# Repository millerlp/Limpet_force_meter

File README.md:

Design files, data, and analysis files from the manuscript "Temperature affects susceptibility of intertidal limpets to bird predation"
Rachel J. Pound, Luke P. Miller, Felicia A. King, Jennifer L. Burnaford
Journal of Experimental Biology 2020 : jeb.213595 doi: 10.1242/jeb.213595

R analysis code and data used in the production of the paper are in the 'R_analysis_files_data/' directory. 

Circuit board designs for the three-dimensional force transducer are in the 'Eagle_files/' directory. These files were
produced with the software Eagle, https://www.autodesk.com/products/eagle/overview. This circuit board is designed to 
attach to an Arduino Due in order to operate. 

Software used to run the 3-dimensional force transducer datalogger are in the 'Arduino_files/' directory. These can
be used with the Arduino software available at https://arduino.cc. The subdirectories in the Arduino_files/ directory should be
installed in the user's "Arduino" directory. 

The Arduino programs here require the following libraries to be installed:
https://github.com/millerlp/RTClib
https://github.com/greiman/SdFat

Limpet_force_meter.ino can be loaded onto the Arduino Due to log data from the force transducer.
Limpet_force_calibration.ino can be loaded to both log data and also to provide a calibration routine that will write data to the SD card as the user hangs weights of various masses off of the 3 axes of the transducer. 

Hardware and software authored by Felicia King and Luke Miller, 2015

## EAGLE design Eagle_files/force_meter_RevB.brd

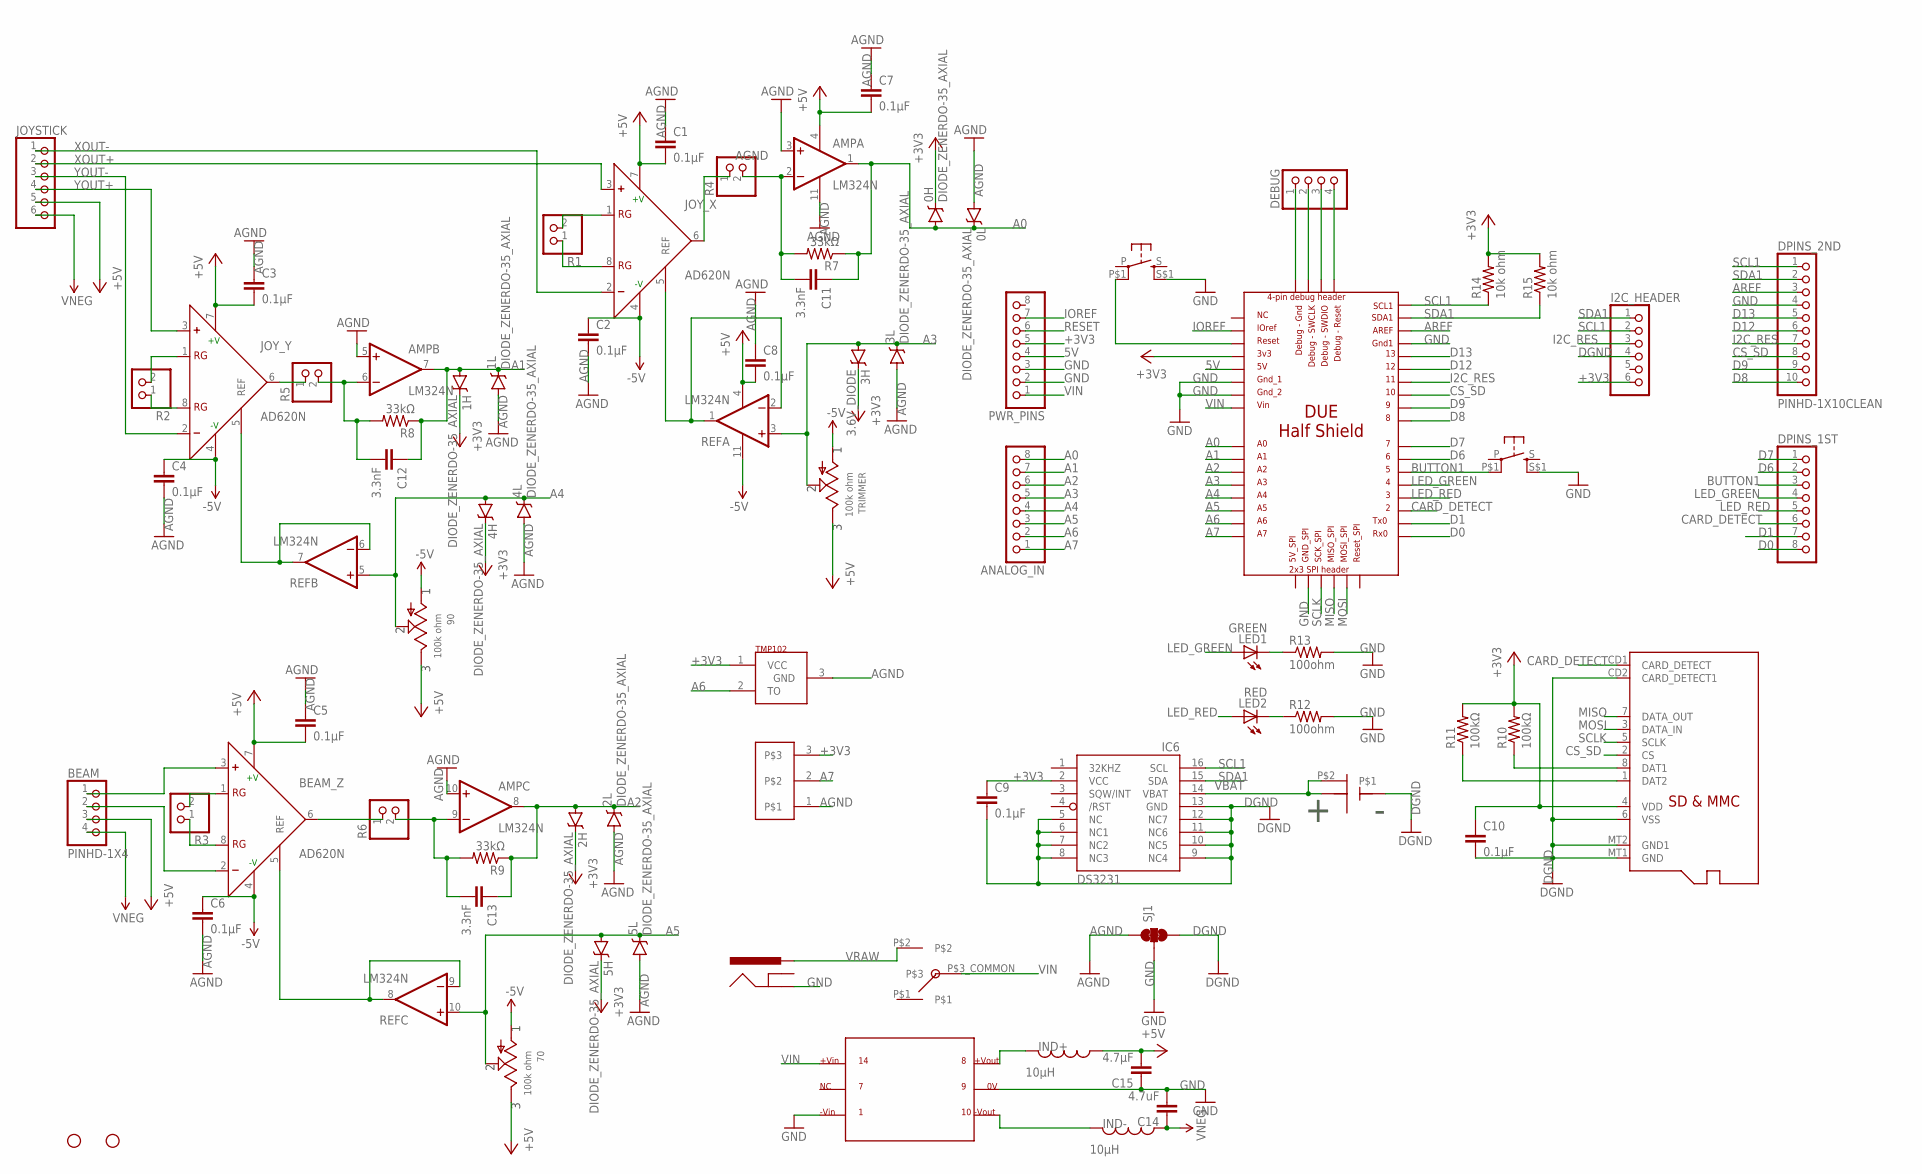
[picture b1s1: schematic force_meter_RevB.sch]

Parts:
0H, 0L, 1H, 1L, 2H, 2L, 3L, 4H, 4L, 5H, 5L: DIODE_ZENERDO-35_AXIAL; DO35-7
3H: 3.6V_DIODE; DO35-7
70, 90: 100k ohm; R-TRIMMER_67W_TT_ELEC
AMP: LM324N; DIL14
ANALOG7_HEADER: PINHD-1X3; 1X03
ANALOG_IN: PINHD-1X8CLEANBIG; 1X08-CLEANBIG
BEAM: PINHD-1X4; 1X04_LOCK
BEAM_Z: AD620N; DIL08
C1, C2, C3, C4, C5, C6, C7, C8, C9, C10: 0.1µF; 0805
C11, C12, C13: 3.3nF; 0805
C14: 4.7uF; 0805
C15: 4.7µF; 0805
DEBUG: PINHD-1X4LOCK; 1X04_LOCK
DPINS_1ST: PINHD-1X8CLEANBIG; 1X08-CLEANBIG
DPINS_2ND: PINHD-1X10CLEAN; 1X10-CLEANBIG
I2C_HEADER: PINHD-1X6LOCK; 1X06-LOCK
IC6: DS3231/SO; SO16W
IND+: 10µH; I_0805
IND-: 10µH; I_0805
INPUT: PUSHBUTTON_DPST_SMD
JOYSTICK: PINHD-1X6LOCK; 1X06-LOCK
JOY_X: AD620N; DIL08
JOY_Y: AD620N; DIL08
LED1: GREEN; CHIPLED_0805
LED2: RED; CHIPLED_0805
PWR_PINS: PINHD-1X8CLEANBIG; 1X08-CLEANBIG
R1, R2, R3, R4, R5, R6: PINHD-1X2; 1X02
R7, R8, R9: 33kΩ; R0805
R10, R11: 100kΩ; R0805
R12, R13: 100ohm; R0805
R14, R15: 10k ohm; R0805
REF: LM324N; DIL14
RESET: PUSHBUTTON; PUSHBUTTON_DPST_SMD
SJ1: JUMPER-PAD-3-NC_BY_TRACE; PAD-JUMPER-3-3OF3_NC_BY_TRACE_YES_SILK_FULL_BOX
STANDOFF1, STANDOFF2: STAND-OFF
TMP102: LM62; SOT23
TRIMMER: 100k ohm; R-TRIMMER_67W_TT_ELEC
U$1: DUE_HALF_SHIELD_A7-ANALOG
U$2: SWITCH_SLIDE_SMD_SPDT; SWITCH_SMD_RA_SPDT
U$3: DC-DC_CONVERTER_DUAL_SUPPLY; DCDC_CONVERTOR-MEV1D
U$11: MICROSD
U$12: CR1220_BATTERY_HOLDERSMD; CR1220_BATTERY_HOLDER_SMD
U$28: POWER_JACK_2,1MM; POWER_JACK_DC_2,1MM

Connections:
5V: PWR_PINS.4, U$1.5V1 (5V)
+3V3: 0H.C, 1H.C, 2H.C, 3H.C, 4H.C, 5H.C, ANALOG7_HEADER.3, C9.1, C10.1, I2C_HEADER.6, IC6.2 (VCC), PWR_PINS.5, R10.2, R11.2, R14.2, R15.2, TMP102.1 (VCC), U$1.3V3, U$11.4 (VDD)
+5V: 70.P$3, 90.P$3, AMP.4 (V+), BEAM.3, BEAM_Z.7 (+V), C1.2, C3.2, C5.2, C7.2, C8.2, C15.2, IND+.P$1 (1), JOYSTICK.5, JOY_X.7 (+V), JOY_Y.7 (+V), REF.4 (V+), TRIMMER.P$3
-5V: 70.P$1, 90.P$1, BEAM.4, BEAM_Z.4 (-V), C6.1, C14.1, IND-.P$1 (1), JOYSTICK.6, TRIMMER.P$1
A0: 0H.A, 0L.C, AMP.1 (OUT), ANALOG_IN.8, C11.1, R7.1, U$1.A0
A1: 1H.A, 1L.C, AMP.7 (OUT), ANALOG_IN.7, C12.1, R8.1, U$1.A1
A2: 2H.A, 2L.C, AMP.8 (OUT), ANALOG_IN.6, C13.1, R9.1, U$1.A2
A3: 3H.A, 3L.C, ANALOG_IN.5, REF.3 (+IN), TRIMMER.P$2, U$1.A3
A4: 4H.A, 4L.C, 90.P$2, ANALOG_IN.4, REF.5 (+IN), U$1.A4
A5: 5H.A, 5L.C, 70.P$2, ANALOG_IN.3, REF.10 (+IN), U$1.A5
A6: ANALOG_IN.2, TMP102.2 (TO), U$1.A6
A7: ANALOG7_HEADER.2, ANALOG_IN.1, U$1.A7
AGND: 0L.A, 1L.A, 2L.A, 3L.A, 4L.A, 5L.A, AMP.3 (+IN), AMP.5 (+IN), AMP.10 (+IN), AMP.11 (V-), ANALOG7_HEADER.1, C1.1, C2.2, C3.1, C4.2, C5.1, C6.2, C7.1, C8.1, SJ1.1, TMP102.3 (GND)
AREF: DPINS_2ND.3, U$1.AREF
BUTTON1: DPINS_1ST.3, INPUT.P$1 (P1), U$1.5
CARD_DETECT: DPINS_1ST.6, U$1.2, U$11.CD1 (CARD_DETECT)
CS_SD: DPINS_2ND.8, U$1.10, U$11.2 (CS)
D0: DPINS_1ST.8, U$1.RX0
D1: DPINS_1ST.7, U$1.TX0
D6: DPINS_1ST.2, U$1.6
D7: DPINS_1ST.1, U$1.7
D8: DPINS_2ND.10, U$1.8
D9: DPINS_2ND.9, U$1.9
D12: DPINS_2ND.6, U$1.12
D13: DPINS_2ND.5, U$1.13
DGND: C9.2, C10.2, I2C_HEADER.4, IC6.5 (NC), IC6.6 (NC1), IC6.7 (NC2), IC6.8 (NC3), IC6.9 (NC4), IC6.10 (NC5), IC6.11 (NC6), IC6.12 (NC7), IC6.13 (GND), SJ1.3, U$11.6 (VSS), U$11.CD2 (CARD_DETECT1), U$11.MT1 (GND), U$11.MT2 (GND1), U$12.GND
GND: C14.2, C15.1, DPINS_2ND.4, INPUT.S$1 (S1), PWR_PINS.2, PWR_PINS.3, R12.2, R13.2, RESET.S$1 (S1), SJ1.2, U$1.GND1, U$1.GND_1, U$1.GND_2, U$1.GND_SPI, U$3.P$1_-VIN, U$3.P$9_0V, U$28.P$2 (GND)
I2C_RES: DPINS_2ND.7, I2C_HEADER.3, U$1.11
IOREF: PWR_PINS.7, U$1.IOREF1 (IOREF)
LED_GREEN: DPINS_1ST.4, LED1.A, U$1.4
LED_RED: DPINS_1ST.5, LED2.A, U$1.3
MISO: U$1.MISO_SPI, U$11.7 (DATA_OUT)
MOSI: U$1.MOSI_SPI, U$11.3 (DATA_IN)
unnamed: JOY_Y.1 (RG), R2.2
unnamed: JOY_X.6 (OUT), R4.1
unnamed: BEAM_Z.6 (OUT), R6.1
unnamed: JOY_X.1 (RG), R1.2
unnamed: JOY_X.8 (RG), R1.1
unnamed: JOY_Y.8 (RG), R2.1
unnamed: JOY_Y.6 (OUT), R5.1
unnamed: BEAM_Z.1 (RG), R3.2
unnamed: BEAM_Z.8 (RG), R3.1
unnamed: AMP.2 (-IN), C11.2, R4.2, R7.2
unnamed: AMP.6 (-IN), C12.2, R5.2, R8.2
unnamed: AMP.9 (-IN), C13.2, R6.2, R9.2
unnamed: IND-.P$2 (2), U$3.P$10_-VOUT
unnamed: IND+.P$2 (2), U$3.P$8_VOUT
unnamed: R10.1, U$11.8 (DAT1)
unnamed: BEAM.2, BEAM_Z.2 (-)
unnamed: BEAM.1, BEAM_Z.3 (+)
unnamed: R11.1, U$11.1 (DAT2)
unnamed: DEBUG.1, U$1.GND_DEBUG
unnamed: LED1.C, R13.1
unnamed: LED2.C, R12.1
unnamed: DEBUG.2, U$1.SWCLK_DEBUG
unnamed: DEBUG.3, U$1.SWDIO_DEBUG
unnamed: DEBUG.4, U$1.RESET_DEBUG
REF_BEAM: BEAM_Z.5 (REF), REF.8 (OUT), REF.9 (-IN)
REF_JOYX: JOY_Y.5 (REF), REF.6 (-IN), REF.7 (OUT)
REF_JOYY: JOY_X.5 (REF), REF.1 (OUT), REF.2 (-IN)
RESET: PWR_PINS.6, RESET.P$1 (P1), U$1.RESET
SCL1: DPINS_2ND.1, I2C_HEADER.2, IC6.16 (SCL), R14.1, U$1.SCL1
SCLK: U$1.SCK_SPI, U$11.5 (SCLK)
SDA1: DPINS_2ND.2, I2C_HEADER.1, IC6.15 (SDA), R15.1, U$1.SDA1
VBAT: IC6.14 (VBAT), U$12.P$1 (VBAT), U$12.P$2
VIN: PWR_PINS.1, U$1.VIN1 (VIN), U$2.P$3_COMMON, U$3.P$14_VIN
VNEG: C2.1, C4.1, JOY_X.4 (-V), JOY_Y.4 (-V), REF.11 (V-)
VRAW: U$2.P$2, U$28.P$1 (PWR)
XOUT+: JOYSTICK.2, JOY_X.3 (+)
XOUT-: JOYSTICK.1, JOY_X.2 (-)
YOUT+: JOYSTICK.4, JOY_Y.3 (+)
YOUT-: JOYSTICK.3, JOY_Y.2 (-)

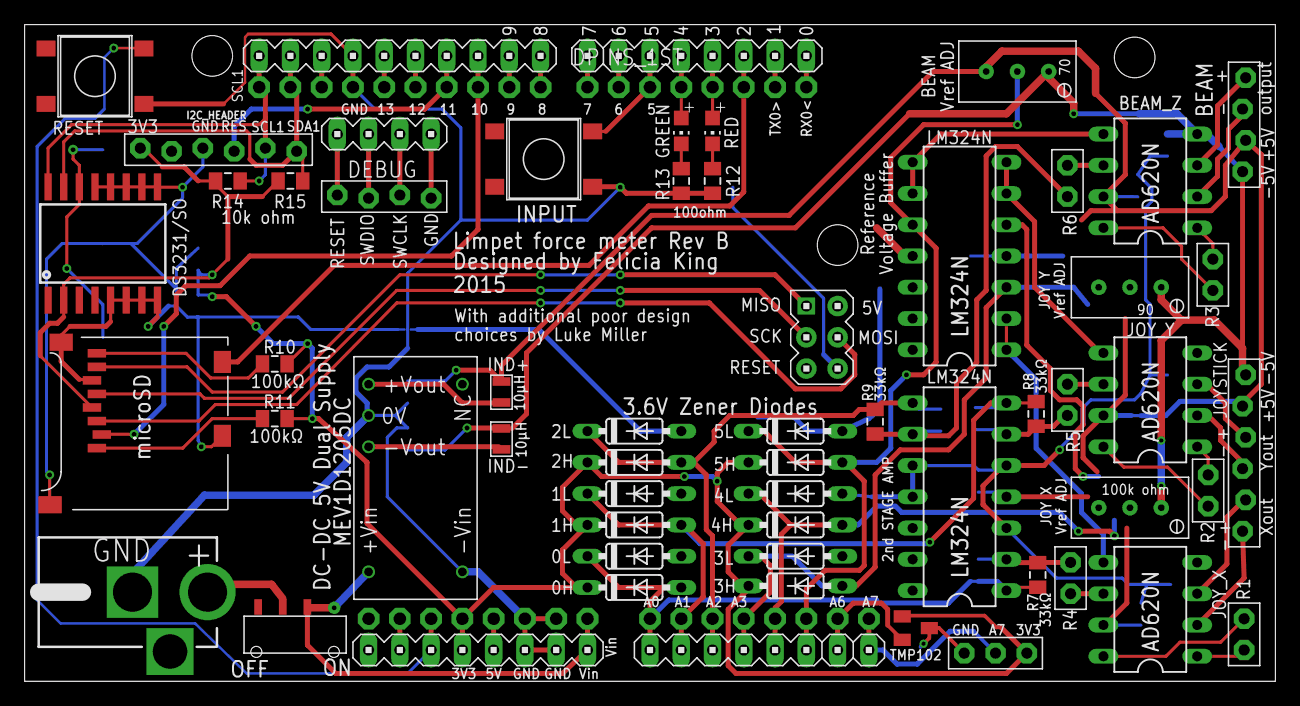
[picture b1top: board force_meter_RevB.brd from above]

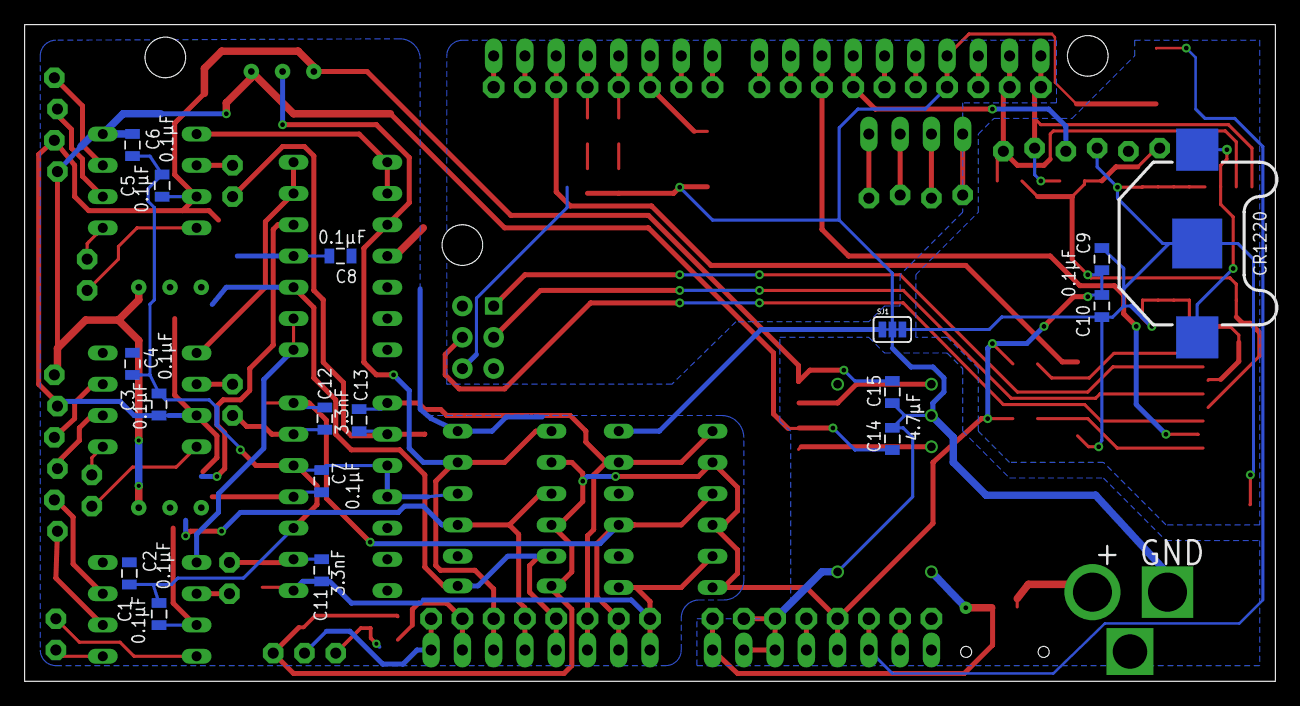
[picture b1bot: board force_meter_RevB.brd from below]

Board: 2 copper layers, 101.6 x 53.3 mm, 77 parts (17 on the bottom side), 72 nets.

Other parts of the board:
STANDOFF3: STAND-OFF

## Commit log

2015-05-07 created board file
2015-05-07 Set maximum board area limits.
2015-05-07 1st complete board draft with small associated schematic changes
2015-05-07 Just moved some things around slightly.
2015-05-07 Found an unconnected wire on the schematic, moved some footprints around
2015-05-09 Added slide switch to schematic
2015-05-09 Moved pieces around the board prior to drawing traces. Inserted the slide switch for raw voltage.
2015-05-09 Started initial routing. Swapped pins from the joystick input header to simplify routing to the in-amps.
2015-05-09 Updating some footprints and separating the analog and digital grounds.
2015-05-09 Fixed the RC filter arrangement on the 2nd stage op-amps for all three inputs. Move the adjust resistors (for 2nd stage amplification setting) in line with the signal line from the AD620s to the LM32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
2015-05-10 Moved the amps around to try to minimize the rats nest. Moved all capacitors to the underside of the board, while all resistors and inductors remain on the top of the board. Added two mounting holes 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
2015-05-10 Started routing the analog lines, and some of the digital lines.
2015-05-13 Corrected unity gain buffer amplifiers for reference voltages into the instrumentation amps.
2015-05-14 Moved the amps around again, wired most of the traces. Discovered that I never connected CS_SD, it is now wired to Due pin D10.
2015-05-14 Removing the old schematic1 since it has some errors and wasn't going to be used again.
2015-05-14 Swapped out I2C header with a 6 pin version that could work with Adafruit I2C OLED display. Moved Reset button to upper corner like the Due's location. Moved LEDs closer to their associated digital p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
2015-05-14 Finished routing top traces, started putting down silkscreen labels. Still need to deal with bottom ground plane.
2015-05-14 Added three separate ground pours for DGND, AGND, and GND.
2015-05-14 Renamed a bunch of the resistors and capacitors so that they are in a more sensible order on the board.
2015-05-14 Fixing some trace widths
2015-05-15 Made sure all the silk screens are appropriate thickness. Added the name and credits to the silkscreen as well.
2015-05-15 Moving files around, added directory for datalogger code
2015-05-15 Cleaning up moved files
2015-05-15 Futzing with the silkscreen
2015-05-15 Adding Felicia's original schematics.
2015-05-18 Aligned all of the diodes to make a little more room. Increased the spacing between the analog ground plane and the neighboring planes. Rewired the A7 analog header so it conforms to standard TMP35, 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
2015-05-21 Tweaking the silkscreen some more. I think this is ready to send off for production.
2015-06-14 Made some minor tweaks to the real time clock startup process, checking that compiling works under Arduino v1.6.4 with my RTClib library.
2015-06-14 Added a description to the eagle project
2015-06-27 Created separate initFileName function, now creates long file name using date and time. Added logfile.sync() and logfile.close() calls so that the file is written to slightly more often than SdFat wo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
2015-06-27 Added a sketch to set the clock time, and cleaned up the basic analog read sketch output.
2015-06-27 Updated .gitignore to skip the eagle backup files
2015-06-27 Started work on a RevB of the shield just in case I ever decide we need a 2nd version that actually works. The VNEG and -5V nets should now all be connected, and the potentiometers sit next to the co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
2015-06-27 I don't think I fixed much on this version, move to RevB for actual fixes.
2015-06-27 Removing the incremental backup files since I don't need them here.
2015-06-28 updating time
2015-06-29 Updated with new time, added comment on purpose.
2015-06-29 Fooling around with logfile.sync to see when it causes a large delay in sampling.
2015-07-03 Adding some extra flashing bits.
2015-07-03 Modified version that includes a calibration routine.
2015-07-03 Modifying gitignore and removing old test file
2015-07-03 Adding version of software that allows user to calibrate the force transducer.
2015-07-03 Adding useful information to the readme for once.
2015-07-13 Converted the calibration mass input from an integer to a floating point value.
2016-05-04 A brief walkthrough of getting the limpet force meter software set up on Arduino.
2016-05-04 Adding notes to the upload guide.
2016-05-04 Adding note about failure to compile more than once, requiring a restart of the Arduino software to allow successful compilation and upload.
2016-05-04 Looks like we had an off-by-one counting error in the F_Values array and the ref_Values array. I'm not sure why this didn't appear as a problem earlier.
2016-05-04 Fixing an off-by-one counting error in the F_Values and ref_Values arrays. We never noticed this manifesting during testing, so I'm not sure what problems it might have caused in the past.
2016-05-05 Just updating the last-edit marker at the top
2016-08-11 Adding board layout diagram
2016-08-11 Ignoring eclipse *.project files
2016-08-11 Functions to import calibration file
2016-08-11 Removing the file path stuff
2016-08-11 Import data with loadCalibFile() function
2016-08-11 Removed file load function since it was dumb, fixed variable misnamed
2016-08-11 Plotting individual axis forces and cumulative force
2016-08-11 Plotting 2 stretches of data with different zero offsets.
2016-08-11 Adding zero-reference line to plots
2016-08-11 Showing plots of the calibration data
2016-08-11 Adding some clarifying comments
2016-08-11 Adding figure output to image for the raw field trace
2016-10-05 Adding path for Luke's dropbox directory
2016-10-27 Re-enabling file loading function
2016-10-27 Updating to use the May data files as well
2016-10-27 Ignoring image files in R_files directory
2016-12-14 Just tweaking the time window for plotting
2016-12-14 Notes on fixing/tweaking the hardware for the limpet force meter
2017-10-27 Adding note about the flaky z-axis connection for the April 26 2016 trial run.
2017-10-27 First commit, putting all analyses in one document
2017-11-03 Updating analysis code, incomplete
2017-12-04 Fixing year reading for 2017 files
2017-12-05 Starting to pick out single events
2017-12-06 Added code to calculate force in Newtons on X Y Z axes for each event time point and write those data to a new output file.
2017-12-07 Ignoring cache
2017-12-07 Fixing calibration file association issue, and starting to come up with a graphical interface to identify peaks and pushes. Still a work in progress.
2017-12-07 Adding in code to allow selection of peaks. Still a work in progress.
2017-12-09 Working version of peak chooser function, generated a set of events for all trials today.
2017-12-09 Implementing algorithm to classify peck and pushes. Need to double-check the output.
2017-12-12 Hiding figure file directory
2017-12-12 Reprocessed events again, but discovered very questionable calibration data on 2016-12-15. I have asked Rachel for the original raw calibration files in hopes that there are usable calibration data i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
2018-01-23 Updated calibration input data
    Some calibration data need to be selectively removed from the calculations because the masses were input incorrectly during calibration. The calibration data for 2016-12-13 need be used for trials on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
2018-01-23 Tweaking the presentation
2018-02-13 Updating peck push algorithm to accomodate 20ms pecks. Also regenerating plots at end.
2018-02-13 Updated with new peck classifier, and re-ran event picker to generate a new set of events and classified events. Word document output updated to reflect the new processing 2018-02-13
2018-05-07 Removed?
2019-08-06 Regenerating things
2019-08-06 Ignore some more stuff
2019-08-06 Adding code to determine the angle of attack on the limpet.
2019-08-06 Ignore log files
2019-08-08 Adding figures and analysis on directionality
2019-08-08 Update gitignore
2019-08-08 Moving files to local directory
2019-08-08 This doesn't belong here.
2019-08-08 Fixing directories and adding
    analysis of shearing dislodgement forces from Denny and Blanchette 2000.
2019-08-12 Revising PeckPush algorithm
    This should now properly handle cases of pecks with 2 samples above the 2N threshold. Updated the output document with the new Peck vs Push categorizations.
2019-08-12 Updated with new Peck vs Push classifications
2019-08-30 Adding limpet aperture area data
    Making new version of Figure 8 plot with Denny & Blanchette data.
2019-12-14 Modifying figures for JEB reviews
    Making 2 panel figure showing time series of a few strikes. Also modifying the 4-panel histogram figure to show mean and standard deviations as well.
2019-12-17 Trying to calc average downward angle
2019-12-20 Angle calculations, timing calcs
    Finished adding the calculations for angle of attack. Also estimated the interval between individual strikes, in milliseconds.
2019-12-24 Adding sample size data
2020-01-02 Breaking out strike interval data
    Added code to break up strike interval data on each date by grouping strikes that occurred less than 10 seconds apart. Also fixed 2 duplicate events in the main dataframe (events3) that should have b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
2020-01-06 Enable the interval code
2020-01-06 Clarifying the 30ms threshold that makes a push
2020-01-06 Re-running
2020-01-06 Show the peakChooser routine code
2020-01-06 Ignoring old useless code
2020-01-06 No longer useful, use .Rmd file code instead
2020-01-06 No longer useful, use code in the .Rmd file instead
2020-01-06 Cleanup
2020-03-06 Generating high-res figures for JEB
2020-03-16 Pictures of the board
